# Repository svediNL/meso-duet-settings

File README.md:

# meso-duet-settings
This repository contains the documents which are/were needed to enable the use of a Duet board on a multi-printhead 3D printer.

## postprocessing
### /gcodes/postprocessing_ws/_edit_retraction.py_
This script is used to alter the retraction command in order to disable/reduce the retaction on the rudder extruder.

A couple of variable should be mentioned in the G-code:
* **E_USED**: number of extruders used in tool.
* **MODE**: replacement mode.
  * **0**: remove all retraction.
  * **1**: E0:1:1:1 disable rudder retraction.
  * **2**: E1:1:1:0 disable rudder retraction.
  * **3**: Ex:1:1:1 reduce rudder retraction.
  * **4**: E1:1:1:x reduce rudder retraction.
* **E_RED**: reduction of rudder retraction when mode 3/4 is used.

The command should be followed by a space-character followed by the actual value:
<code> ;[COMMAND] SPACE [VALUE] </code>

## _C O N T E N T S_
Repository contents:

## _/configurations_
Contains the configuration files placed in the _/sys_-folder on the SD-card on the Duet.
* **/config full extruder** contains a _/sys_-folder generated by the [reprap-firmware configurator](https://configurator.reprapfirmware.org/)  
* **/manualconfig** contains the custom _config.g_-file with additional support files.

## _/gcodes_
Contains gcodes for testing and postprocessing scripts.
* **/postprocessing_ws** contains the post processing scipts and acts as a workspace for testing.

## _/init_SD_
Contains the contents of the SD-card on first contact.
* **/filaments** contains G-code macros for loading/unloading filaments.
* **/gcodes** contains G-codes for printing.
* **/macros** contains G-code macros that can be excuted via the web interface.
* **/sys** contains all G-code files which add to the basic functionality of the machine.
* **/System Volume Information** contains some sort of information file.
* **/www** spooky HTLM stuff.

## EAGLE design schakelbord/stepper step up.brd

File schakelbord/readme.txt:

Het .brd bestand bevat het fysieke CAD ontwerp van het schakelbord en kan rechtstreeks naar eurocircuits geupload worden voor realisatie.

Het ontwerp is gemaakt in EAGLE

Dit ontwerp is een revisie van het eerste bord en heeft gaten die groot genoeg zouden moeten zijn voor de headers en termminals. Daarnaast zijn de traces verdikt.

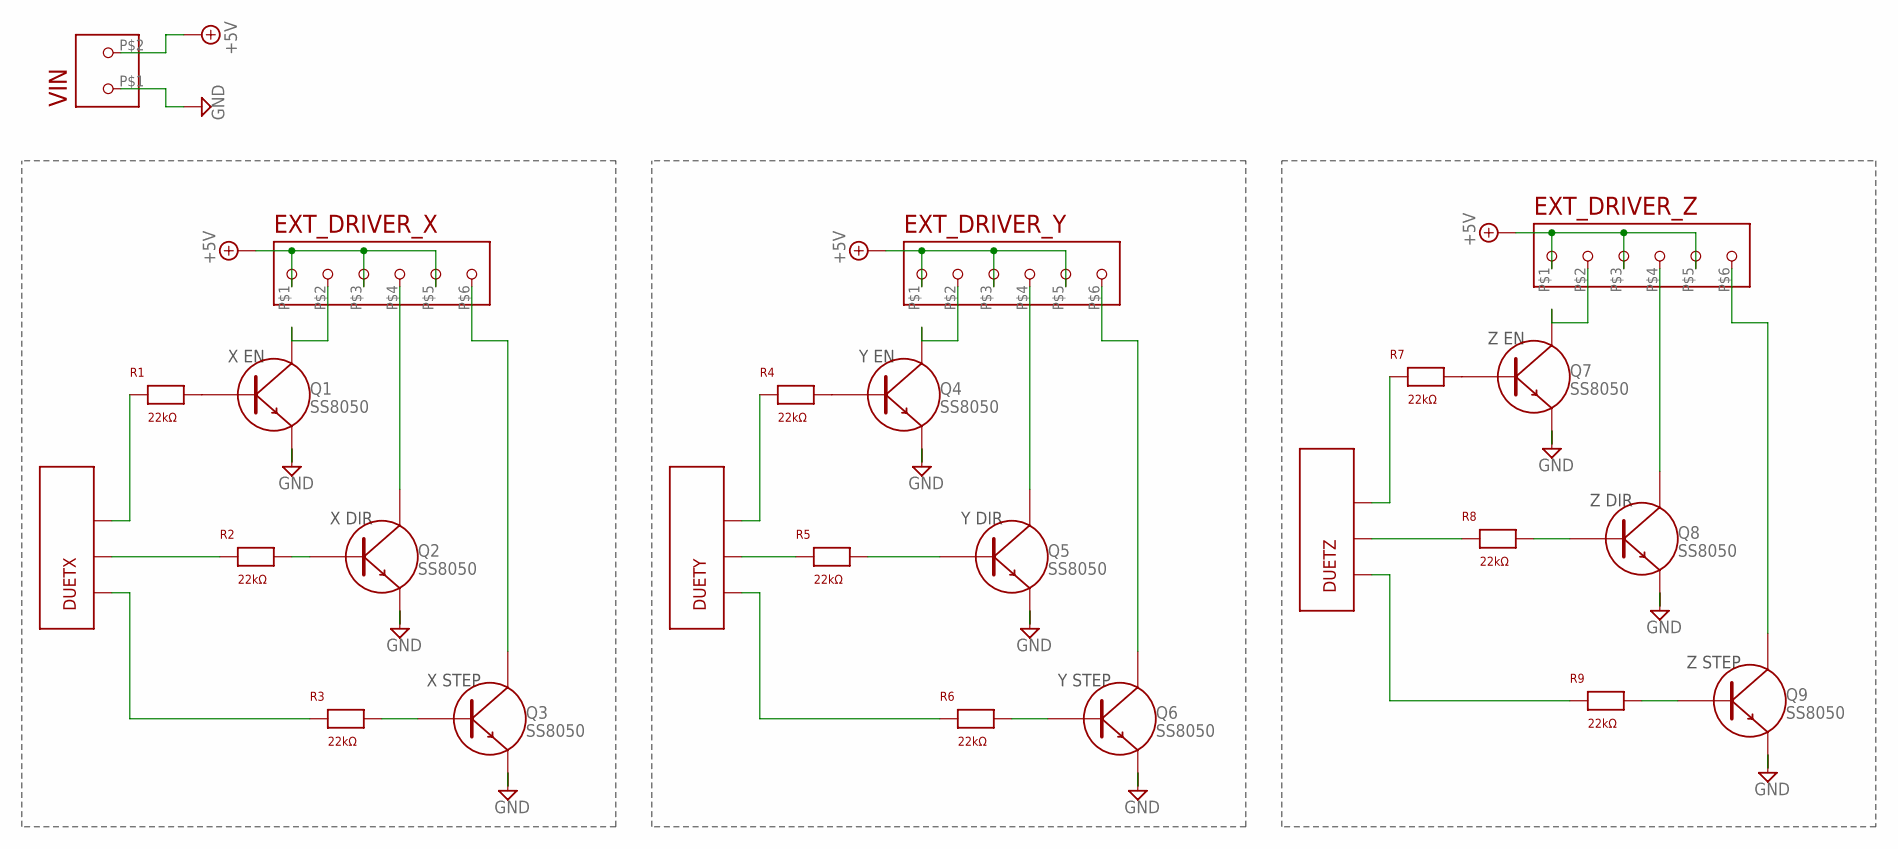
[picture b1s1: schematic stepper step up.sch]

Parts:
DUETX: BKL_3XPINHEAD
DUETY: BKL_3XPINHEAD
DUETZ: BKL_3XPINHEAD
EXT_DRIVER_X: SCREW_X6
EXT_DRIVER_Y: SCREW_X6
EXT_DRIVER_Z: SCREW_X6
Q1, Q2, Q3, Q4, Q5, Q6, Q7, Q8, Q9: SS8050; NPN_SS8050
R1, R2, R3, R4, R5, R6, R7, R8, R9: 22kΩ; VERT_RES
VIN: SCREW_X2

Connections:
+5V: EXT_DRIVER_X.P$1, EXT_DRIVER_X.P$3, EXT_DRIVER_X.P$5, EXT_DRIVER_Y.P$1, EXT_DRIVER_Y.P$3, EXT_DRIVER_Y.P$5, EXT_DRIVER_Z.P$1, EXT_DRIVER_Z.P$3, EXT_DRIVER_Z.P$5, VIN.P$2
GND: Q1.E, Q2.E, Q3.E, Q4.E, Q5.E, Q6.E, Q7.E, Q8.E, Q9.E, VIN.P$1
unnamed: Q9.B, R9.P$2
unnamed: DUETZ.P$1, R9.P$1
unnamed: DUETZ.P$2, R8.P$1
unnamed: Q8.B, R8.P$2
unnamed: DUETZ.P$3, R7.P$1
unnamed: Q7.B, R7.P$2
unnamed: Q6.B, R6.P$2
unnamed: DUETY.P$1, R6.P$1
unnamed: DUETY.P$2, R5.P$1
unnamed: Q5.B, R5.P$2
unnamed: DUETY.P$3, R4.P$1
unnamed: Q4.B, R4.P$2
unnamed: Q1.B, R1.P$2
unnamed: DUETX.P$3, R1.P$1
unnamed: DUETX.P$2, R2.P$1
unnamed: Q2.B, R2.P$2
unnamed: DUETX.P$1, R3.P$1
unnamed: Q3.B, R3.P$2
X_DIR-: EXT_DRIVER_X.P$4, Q2.C
X_EN-: EXT_DRIVER_X.P$2, Q1.C
X_STEP-: EXT_DRIVER_X.P$6, Q3.C
Y_DIR-: EXT_DRIVER_Y.P$4, Q5.C
Y_EN-: EXT_DRIVER_Y.P$2, Q4.C
Y_STEP-: EXT_DRIVER_Y.P$6, Q6.C
Z_DIR-: EXT_DRIVER_Z.P$4, Q8.C
Z_EN-: EXT_DRIVER_Z.P$2, Q7.C
Z_STEP-: EXT_DRIVER_Z.P$6, Q9.C

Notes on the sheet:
X STEP
X DIR
X EN
Y STEP
Y DIR
Y EN
Z STEP
Z DIR
Z EN

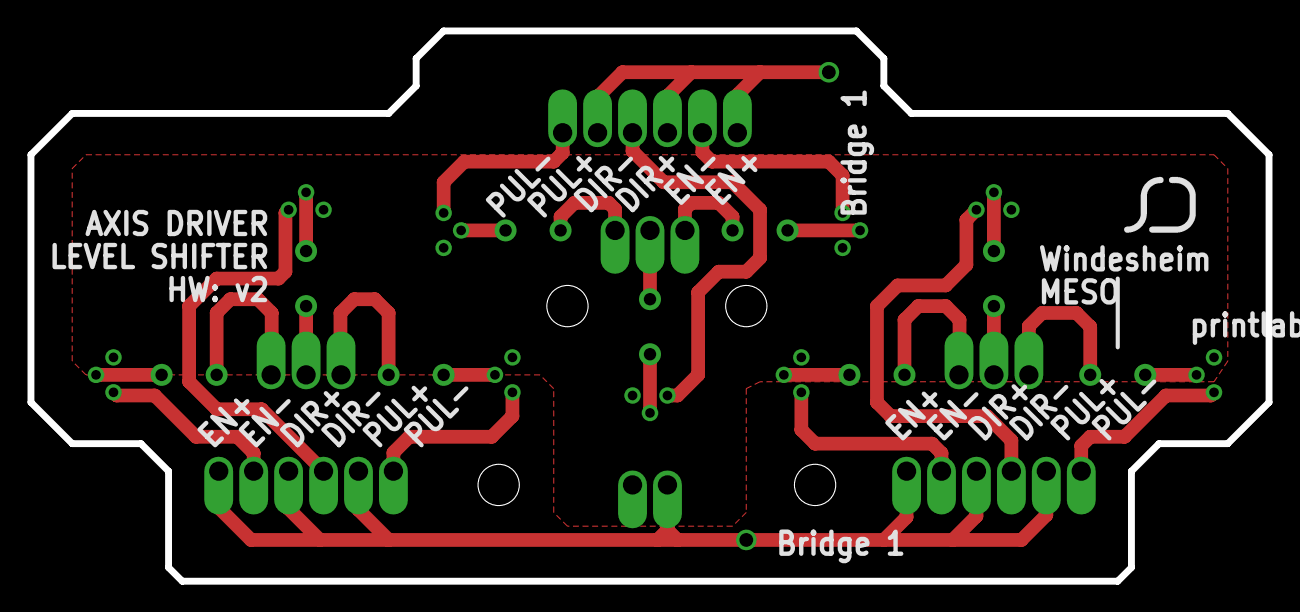
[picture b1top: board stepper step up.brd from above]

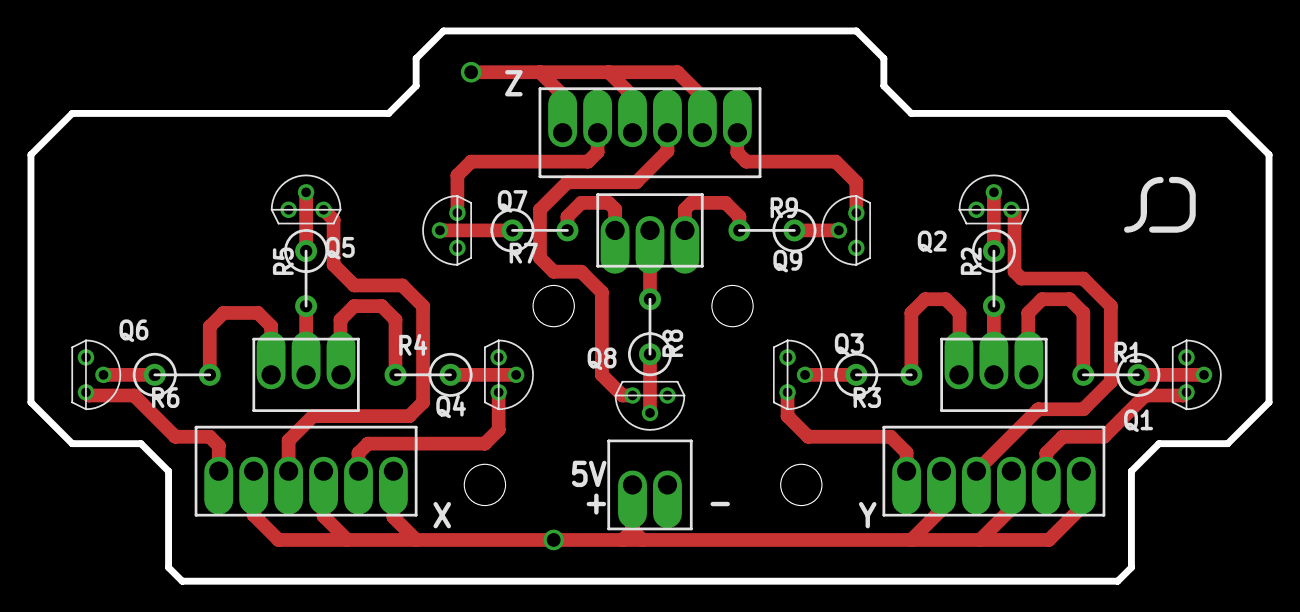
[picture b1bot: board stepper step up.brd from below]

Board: 2 copper layers, 90.0 x 40.0 mm, 25 parts (18 on the bottom side), 29 nets.

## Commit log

2018-05-08 first configurations
2018-05-08 initial added
2018-05-14 Added pushrod calculations
    To calculate the steps/mm resolution as if it were a 3mm filament extruder
2018-05-14 pushrod
2018-05-14 added NaN/default detection
2018-05-29 Clean up of config.g
    Added more comments and changed some settings.
2018-06-03 From old macbook
    Added postprocessing script
2018-06-06 Update on postprocessing script
    Added functions to find the location of and extract the extrusion
    retraction parameter.
    Next to add: replacing the extrusion parameter
2018-06-06 Added external triggers to config
    Location of the endstops was determined and the g-code for external triggers was added
2018-06-08 Now functional in slic3r
    Python script now works with slic3r and doesn't give the excecutable error.
2018-06-10 Update on README
    include instructions for manipulate_retraction.py
2018-06-11 Functional in slic3r
    Updated structure to make every post processing function a part of the gcode class. Also added functionality to add certain parameters via the gcode. Script is now executable by slic3r.
2018-06-11 edit_retraction
2018-07-24 Additional docs added
    Added switchboard eagle file and g-code generators
